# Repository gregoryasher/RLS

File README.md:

# Remote Lab System: Base Station
The Remote Lab System is a system designed for the University of Washington Bothell campus's Electrical Engineering department. This was a Capstone (or Senior) project that concluded our degrees at the University of Washington. We are a group of Computer Engineering students who were enrolled in the program from 2015 to 2017 when we graduated summer quarter. The development of this project was broken up into Spring and Summer quarter 2017.

# Starting Notes
When we chose this as our project we were initially informed the system did not function. At all. What we found towards the end of our first quarter was the system did not work because previous teams did not create or test any of the components or any code to do so. It became apparent we needed to completely redesign the system and create all the code.

We created a project and work schedule and dove in. These schedules were essential to the success of our project.

# Goals
This was the fourth iteration of the Base Station and our design goals were to: 
Add an additional Intronix LogicPort logic analyzer to support a maximum total of 68-channels
Add an 16-bit Analog-to-Digital Converter (ADC)
Improve heat dissipation from linear regulators
Design a stable chassis
Update Graphical User Interface (GUI)
Improve software robustness

# Purpose
The Remote Lab System is designed to allow students to work on lab experiments remotely away from campus, or the lab facilities. This system is a learning tool and study aid allowing students to have unlimited access, at any time of day, to their required lab equipment. Dr. Arnold Berger at the University of Washington Bothell conducted research showing that when students were given the ability to work remotely, the peak times were between midnight and 4:00 am. His research also concluded that female students spent more time connected to the system than male students, and also generally received higher grades on related course content.

While no version of the Remote Lab System has been officially implemented in coursework, we believe our project will increase students understanding of hardware integration by allowing them to quickly change various settings on daughterboard experiments and observe their changes in real time.

# Conclusion
At the end of our Capstone program in Summer quarter 2017 we had successfully achieved our goals. 

We added an additional logic analyzer: allowing the use of the two operating independently (two 34-channel logic analyzers) or dual support (one 68-channel logic analyzer) based on the configuration of the attached daughterboard.

We added a 16-bit ADC, effectively increasing the accuracy of node voltage measurements made by the system by 256 times.

We successfully solved the heat dissipation issue on the linear regulators by increasing the heatsink size and adding a thermally controlled fan circuit. 

We purchased and built a galvanized steel chassis for the system to be housed, complete with rubber feet to reduce vibrations caused by the fan. The motherboard's daughterboard connectors protrude from the lid such that no daughterboard will have clearance issues on the lid. The motherboard is mounted to the lid using brass standoffs threaded to the lid. The Velleman Oscilloscope/Function Generator system is securely mounted to the bottom of the chassis. Connector cables were made long enough such that the lid may be removed from the chassis and placed flat beside it. The fan is securely mounted to the chassis with no interference on the motherboard and in direct line with all four linear regulator heatsinks.

We successfully updated the GUI to improve security and user lockouts. The user can no longer send updated board information to a daughterboard not installed. The user can no longer change settings on a daughterboard not installed. The user is forced to check which board is installed before making any settings changes. 

The GUI now automatically detects the correct communications port for the Remote Lab System. If the Remote Lab System is not detected upon program start-up, a prompt appears warning the user.

Pressing the "Update Board" button now actually updates the board with the user's desired daughterboard settings.

Pressing the "Check Board" button now actually sends a request to read the daughterboard's boardID pin states. It also receives the correct values that were read.

Linear regulators now have supporting code and the values change based on the constructor's inputs. It should be noted that these devices in previous iterations never operated due to a lack of supporting code.

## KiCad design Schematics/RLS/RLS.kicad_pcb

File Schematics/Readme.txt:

This folder contains the schematics for the Motherboard of the Remote Lab System.

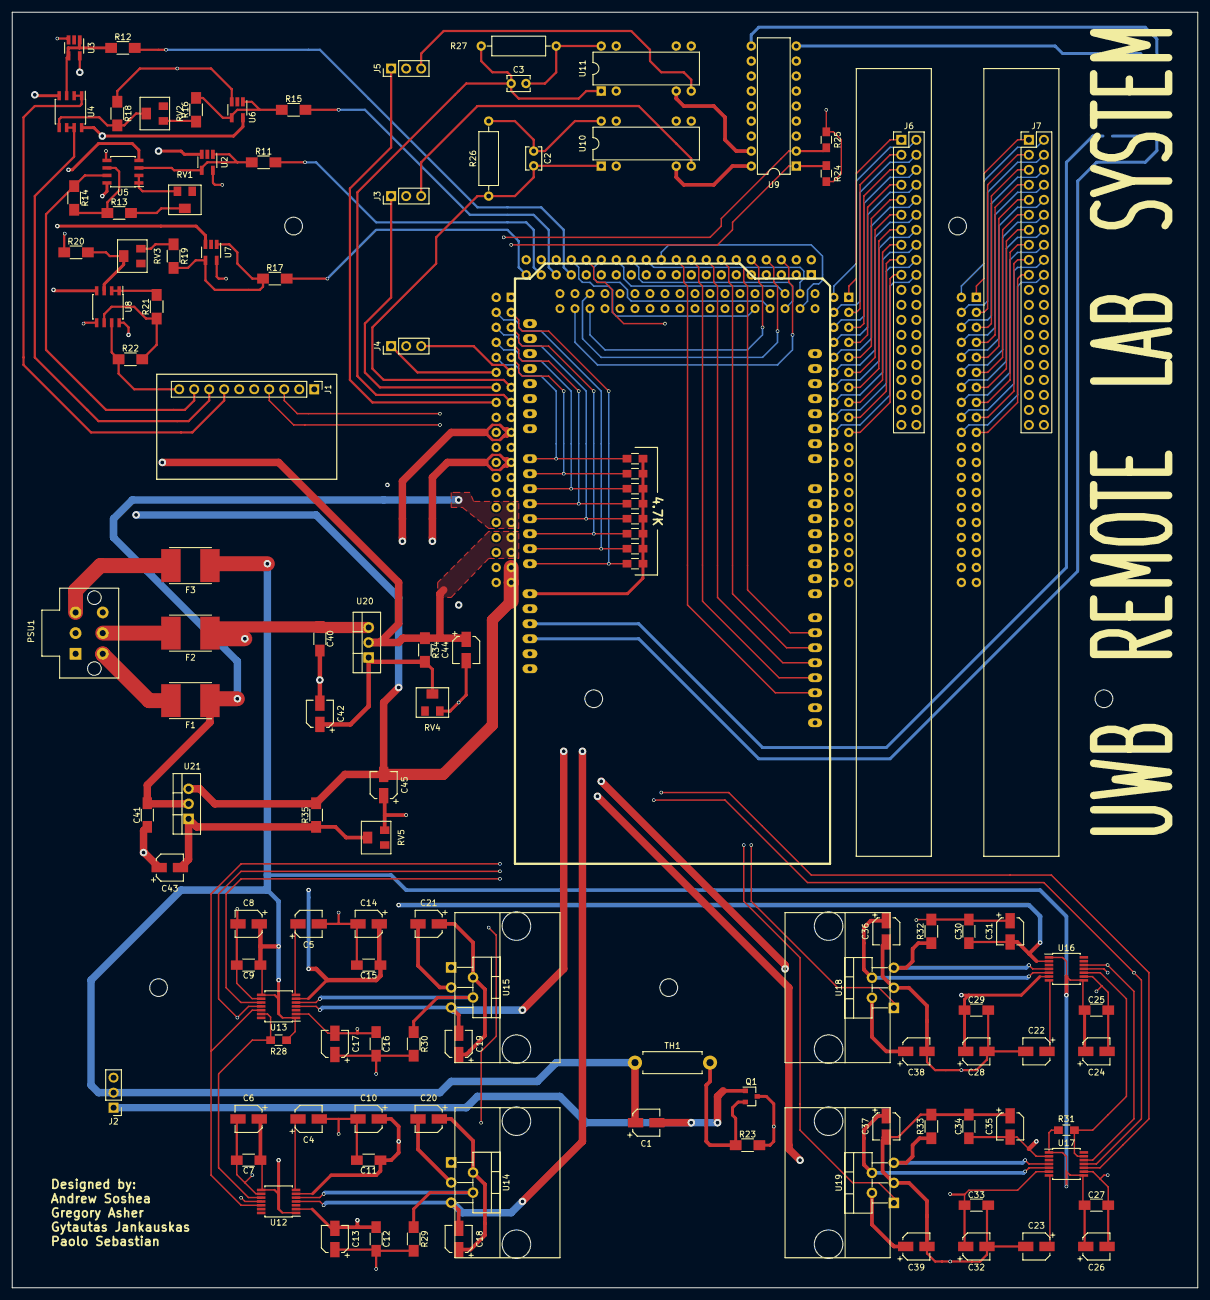
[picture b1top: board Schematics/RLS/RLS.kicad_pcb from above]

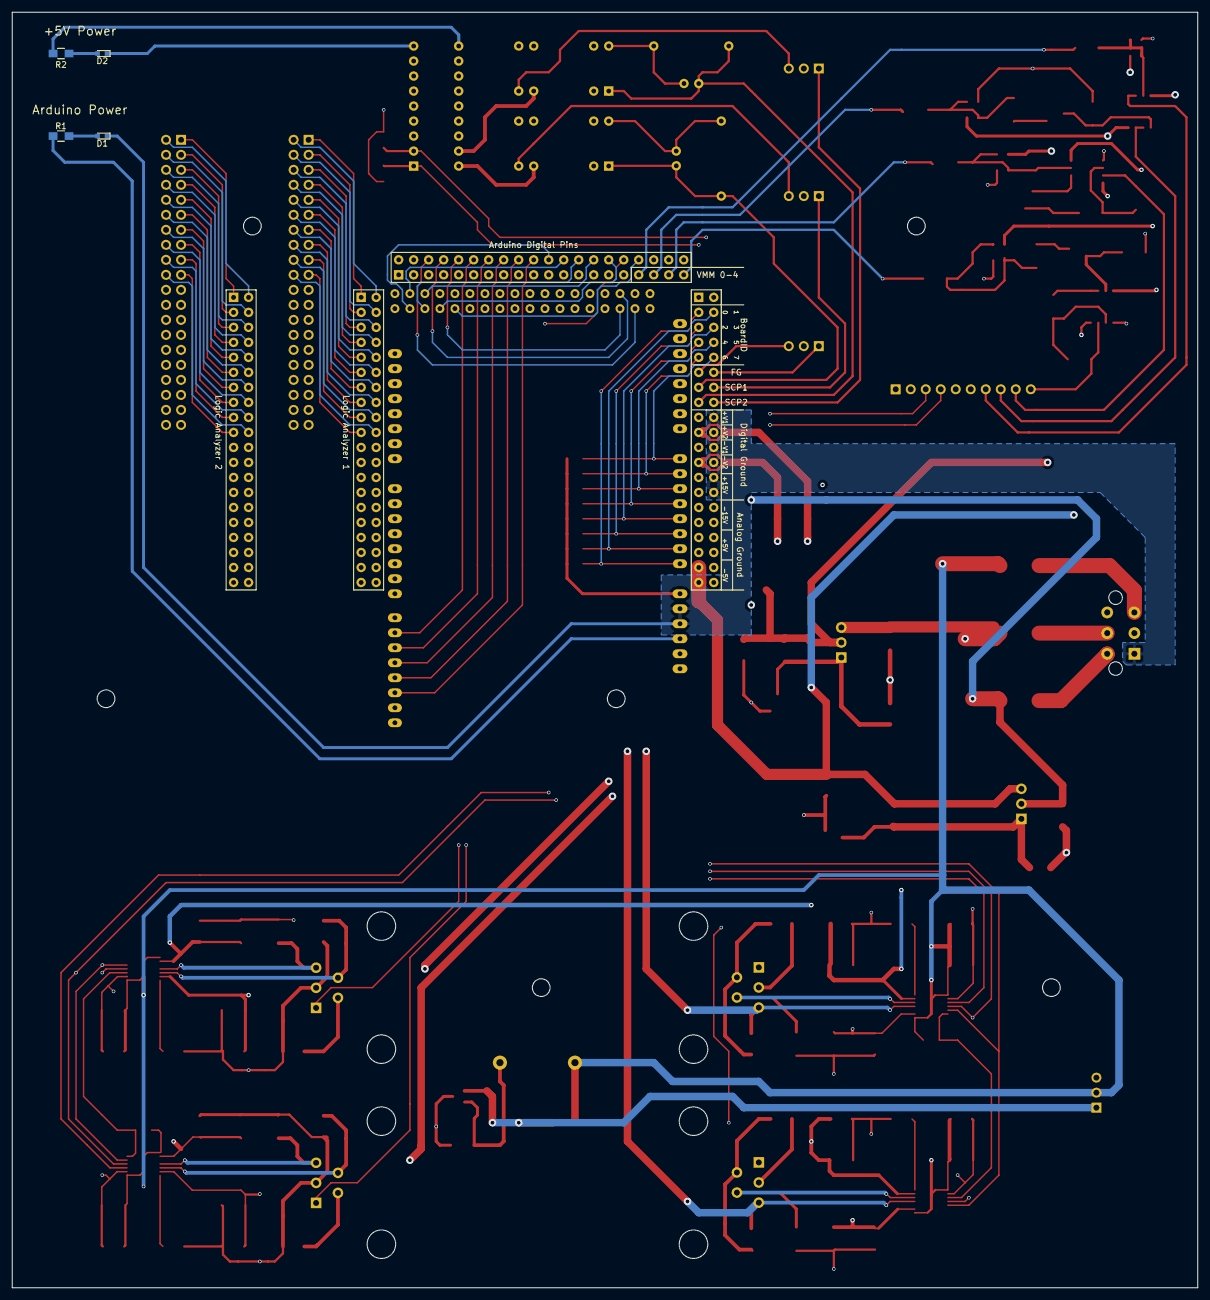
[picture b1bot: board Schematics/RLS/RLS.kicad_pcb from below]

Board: 4 copper layers, 200.7 x 215.9 mm, 122 parts (4 on the bottom side), 188 nets.

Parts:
C1, C6, C8, C10, C13, C14, C17, C18, C19, C20, C21, C24, C26, C28, C31, C32, C35, C36, C37, C38, C39, C42, C43: 10uF; CP_Elec_4x5.3
C2, C3: 15pF; C_Disc_D3.8mm_W2.6mm_P2.50mm
C4, C5, C22, C23, C44, C45: 1uF; CP_Elec_4x5.3
C7, C9, C11, C12, C15, C16, C25, C27, C29, C30, C33, C34, C40, C41: 0.1uF; C_1206_HandSoldering
D1: AD_LED; LED_0603
D2: +5V_LED; LED_0603
DB1: DaughterBoard_Connectors; Daughterboard_4_Conn
F1: 1A; Fuse_SMD_Custom
F2: 1.5A; Fuse_SMD_Custom
F3: 4A; Fuse_SMD_Custom
J1: ADS1115; Pin_Header_Straight_1x10_Pitch2.54mm
J2: DC_Fan; Pin_Header_Straight_1x03_Pitch2.54mm
J3: Velleman_Probe1; Pin_Header_Straight_1x03_Pitch2.54mm
J4: Velleman_FuncGen; Pin_Header_Straight_1x03_Pitch2.54mm
J5: Velleman_Probe2; Pin_Header_Straight_1x03_Pitch2.54mm
J6: Logic_Analyzer1; Pin_Header_Straight_2x20_Pitch2.54mm
J7: Logic_Analyzer2; Pin_Header_Straight_2x20_Pitch2.54mm
PSU1: DIN_5; Molex_2x3_3.5mm
Q1: BS170; SOT-23
R1, R2, R3, R4, R5, R6, R7, R8, R9, R10, R24, R25, R28, R31: 4.7K; R_0805_HandSoldering
R11, R12, R34, R35: 120; R_1206_HandSoldering
R13: 768; R_1206_HandSoldering
R14, R21, R22, R23: 1K; R_1206_HandSoldering
R15, R17, R18, R20: 10K; R_1206_HandSoldering
R16, R19: 9.76K; R_1206_HandSoldering
R26, R27: 9M; R_Axial_DIN0309_L9.0mm_D3.2mm_P12.70mm_Horizontal
R29, R30, R32, R33: 1.78K; R_1206_HandSoldering
RV1, RV2, RV3: 500; Potentiometer_Trimmer_Bourns_PVG5A
RV4, RV5: 1K; Potentiometer_Trimmer_Bourns_PVG5A
TH1: 3K_NTC; R_Axial_DIN0411_L9.9mm_D3.6mm_P12.70mm_Horizontal
U1: ARDUINO_MEGA_SHIELD
U2, U3, U6, U7: RB496EATR; SOT-23-5_HandSoldering
U4, U5, U8: NE5532; SOIC-8_3.9x4.9mm_Pitch1.27mm
U9: ULN2803A; DIP-18_W7.62mm
U10, U11: RA30421051; DIP-8(14)_W7.62mm
U12, U13, U16, U17: AD5293; TSSOP-14_4.4x5mm_Pitch0.65mm
U14, U15: LT3015; TO-220-5_Vertical_Type1_w_Heatsink
U18, U19: LT1963; TO-220-5_Vertical_Type1_w_Heatsink
U20: LM317T; TO-220_Vertical
U21: LM337T; TO-220_Vertical

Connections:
+5V: C1.1, C6.1, C7.1, C8.1, C9.1, C24.1, C25.1, C26.1, C27.1, F3.1, J1.1, J2.2, R2.1, R3.2, R4.2, R5.2, R6.2, R7.2, R8.2, R9.2, R10.2, R24.1, R25.1, R28.2, R31.2, TH1.1, U1.V_IN, U9.10, U10.2, U11.2, U12.1, U12.8, U13.1, U13.8, U16.1, U16.8, U17.1, U17.8
+5V_R: C44.1, DB1.33, DB1.35, R34.1, U3.5, U20.2
+15V: C10.1, C11.1, C14.1, C15.1, C28.1, C29.1, C32.1, C33.1, C38.1, C39.1, C40.1, DB1.25, DB1.27, F2.1, U4.8, U5.8, U6.5, U8.8, U12.6, U13.6, U16.6, U17.6, U18.2, U19.2, U20.3
+V1: C36.1, DB1.17, U16.5, U18.4
+V1_SHDN: U1.AD9, U18.1
+V2: C37.1, DB1.19, U17.5, U19.4
+V2_SHDN: U1.AD8, U19.1
-5V_R: C45.2, DB1.37, DB1.39, R35.2, U2.3, U21.3
-15V: C12.1, C13.2, C16.1, C17.2, C20.2, C21.2, C30.1, C31.2, C34.1, C35.2, C41.2, DB1.29, DB1.31, F1.1, U4.4, U5.4, U7.3, U8.4, U12.2, U13.2, U14.3, U15.3, U16.2, U17.2, U21.2
-V1: C18.2, DB1.21, U12.4, U14.5
-V1_SHDN: U1.AD11, U14.1
-V2: C19.2, DB1.23, U13.4, U15.5
-V2_SHDN: U1.AD10, U15.1
/+5V_-5V_Regulators/+ADJ: C42.1, R34.2, RV4.2, U20.1
/+5V_-5V_Regulators/-ADJ: C43.2, R35.1, RV5.2, U21.1
/ADC_Divder_&_DC_Fan/+5_OVP: R12.1, U3.1, U3.4, U4.3
/ADC_Divder_&_DC_Fan/+15_ADJ: R16.1, RV2.1
/ADC_Divder_&_DC_Fan/+15_DIV: R18.2, RV2.2, U4.5
/ADC_Divder_&_DC_Fan/+15_OVP: R15.1, R16.2, U6.1, U6.4
/ADC_Divder_&_DC_Fan/-5_ADJ: R13.2, RV1.2
/ADC_Divder_&_DC_Fan/-5_BUFF: RV1.3, U5.1, U5.2
/ADC_Divder_&_DC_Fan/-5_INV: R13.1, R14.2, U5.6
/ADC_Divder_&_DC_Fan/-5_OVP: R11.1, U2.1, U2.4, U5.3
/ADC_Divder_&_DC_Fan/-15_ADJ: R19.1, RV3.3
/ADC_Divder_&_DC_Fan/-15_BUFF: R21.2, U8.1, U8.2
/ADC_Divder_&_DC_Fan/-15_DIV: R20.2, RV3.2, U8.3
/ADC_Divder_&_DC_Fan/-15_INV: R21.1, R22.2, U8.6
/ADC_Divder_&_DC_Fan/-15_OVP: R17.1, R19.2, U7.1, U7.4
/ADC_Divder_&_DC_Fan/FAN_GND: C1.2, J2.1, Q1.1
/ADC_Divder_&_DC_Fan/VGS_FAN: Q1.2, R23.1, TH1.2
/ARD_LED: D1.2, R1.2
/BID0: DB1.3, R3.1, U1.AD0
/BID1: DB1.4, R7.1, U1.AD1
/BID2: DB1.5, R4.1, U1.AD2
/BID3: DB1.6, R8.1, U1.AD3
/BID4: DB1.7, R5.1, U1.AD4
/BID5: DB1.8, R9.1, U1.AD5
/BID6: DB1.9, R6.1, U1.AD6
/BID7: DB1.10, R10.1, U1.AD7
/DIN5: F3.2, PSU1.3
/DIN+15: F2.2, PSU1.5
/DIN-15: F1.2, PSU1.4
/Negative_Regulators/-SDO_SDI: R28.1, U12.10, U13.13
/Negative_Regulators/-V1_ADJ: R29.1, U12.5, U14.4
/Negative_Regulators/-V1_EX_C: C4.1, U12.7
/Negative_Regulators/-V2_ADJ: R30.1, U13.5, U15.4
/Negative_Regulators/-V2_EX_C: C5.1, U13.7
/PSU_LED: D2.2, R2.2
/Positive_Regulators/+SDO_SDI: R31.1, U16.10, U17.13
/Positive_Regulators/+V1_ADJ: R32.1, U16.4, U18.5
/Positive_Regulators/+V1_EX_C: C22.1, U16.7
/Positive_Regulators/+V2_ADJ: R33.1, U17.4, U19.5
/Positive_Regulators/+V2_EX_C: C23.1, U17.7
/Scope_Probe_Gain/+SCP1: J3.3, U10.4
/Scope_Probe_Gain/+SCP2: J5.3, U11.4
/Scope_Probe_Gain/SCP1_10X: C2.1, R26.2, U10.8
/Scope_Probe_Gain/SCP2_10X: C3.2, R27.1, U11.8
AA12: R24.2, U1.AD12, U9.1
AA13: R25.2, U1.AD13, U9.2
AA14: DB1.2, U1.AD14
AA15: DB1.1, U1.AD15
AD9: DB1.52, U1.9
AD10: DB1.54, U1.10
AD11: DB1.56, U1.11
AD12: DB1.58, U1.12
AD13: DB1.60, U1.13
AD22: DB1.62, U1.22
AD23: DB1.64, U1.23
AD24: DB1.66, U1.24
AD25: DB1.68, U1.25
AD26: DB1.70, U1.26
AD27: DB1.72, U1.27
AD28: DB1.74, U1.28
AD29: DB1.76, U1.29
AD30: DB1.78, U1.30
AD31: DB1.80, U1.31
AD32: DB1.41, U1.32
AD33: DB1.43, U1.33
AD34: DB1.45, U1.34
AD35: DB1.47, U1.35
AD36: DB1.49, U1.36
AD37: DB1.51, U1.37
AD38: DB1.53, U1.38
AD39: DB1.55, U1.39
AD40: DB1.57, U1.40
AD41: DB1.59, U1.41
AD42: DB1.61, U1.42
AD43: DB1.63, U1.43
AD44: DB1.65, U1.44
AD45: DB1.67, U1.45
AD46: DB1.69, U1.46
AD47: DB1.71, U1.47
AD_LED: R1.1, U1.5V
AGND: C4.2, C5.2, C6.2, C7.2, C8.2, C9.2, C10.2, C11.2, C12.2, C13.1, C14.2, C15.2, C16.2, C17.1, C18.1, C19.1, C20.1, C21.1, C22.2, C23.2, C24.2, C25.2, C26.2, C27.2, C28.2, C29.2, C30.2, C31.1, C32.2, C33.2, C34.2, C35.1, C36.2, C37.2, C38.2, C39.2, C40.2, C41.1, C42.2, C43.1, C44.2, C45.1, D2.1, DB1.30, DB1.32, DB1.34, DB1.36, DB1.38, DB1.40, J1.2, J1.5, PSU1.2, Q1.3, R18.1, R20.1, R23.2, R29.2, R30.2, R32.2, R33.2, RV4.3, RV5.3, U2.5, U3.3, U5.5, U6.3, U7.5, U8.5, U9.9, U12.9, U13.9, U14.2, U15.2, U16.9, U17.9, U18.3, U19.3
AIN0: J1.7, U4.1, U4.2
AIN1: J1.8, U4.6, U4.7
AIN2: J1.9, R14.1, U5.7
AIN3: J1.10, R22.1, U8.7
DGND: D1.1, DB1.18, DB1.20, DB1.22, DB1.24, DB1.26, DB1.28, PSU1.1, U1.GND1, U1.GND2
L1CLK1: DB1.100, J6.20
L1CLK2: DB1.120, J6.40
L1D0: DB1.81, J6.1
L1D1: DB1.82, J6.2
L1D2: DB1.83, J6.3
L1D3: DB1.84, J6.4
L1D4: DB1.85, J6.5
L1D5: DB1.86, J6.6
L1D6: DB1.87, J6.7
L1D7: DB1.88, J6.8
L1D8: DB1.91, J6.11
L1D9: DB1.92, J6.12
L1D10: DB1.93, J6.13
L1D11: DB1.94, J6.14
L1D12: DB1.95, J6.15
L1D13: DB1.96, J6.16
L1D14: DB1.97, J6.17
L1D15: DB1.98, J6.18
L1D16: DB1.101, J6.21
L1D17: DB1.102, J6.22
L1D18: DB1.103, J6.23
L1D19: DB1.104, J6.24
L1D20: DB1.105, J6.25
L1D21: DB1.106, J6.26
L1D22: DB1.107, J6.27
L1D23: DB1.108, J6.28
L1D24: DB1.111, J6.31
L1D25: DB1.112, J6.32
L1D26: DB1.113, J6.33
L1D27: DB1.114, J6.34
L1D28: DB1.115, J6.35
L1D29: DB1.116, J6.36
L1D30: DB1.117, J6.37
L1D31: DB1.118, J6.38
L1GND: DB1.89, DB1.90, DB1.99, DB1.109, DB1.110, DB1.119, J6.9, J6.10, J6.19, J6.29, J6.30, J6.39
L2CLK1: DB1.140, J7.20
L2CLK2: DB1.160, J7.40
L2D0: DB1.121, J7.1
L2D1: DB1.122, J7.2
L2D2: DB1.123, J7.3
L2D3: DB1.124, J7.4
L2D4: DB1.125, J7.5
L2D5: DB1.126, J7.6
L2D6: DB1.127, J7.7
L2D7: DB1.128, J7.8
L2D8: DB1.131, J7.11
L2D9: DB1.132, J7.12
L2D10: DB1.133, J7.13
L2D11: DB1.134, J7.14
L2D12: DB1.135, J7.15
L2D13: DB1.136, J7.16
L2D14: DB1.137, J7.17
L2D15: DB1.138, J7.18
L2D16: DB1.141, J7.21
L2D17: DB1.142, J7.22
L2D18: DB1.143, J7.23
L2D19: DB1.144, J7.24
L2D20: DB1.145, J7.25
L2D21: DB1.146, J7.26
L2D22: DB1.147, J7.27
L2D23: DB1.148, J7.28
L2D24: DB1.151, J7.31
L2D25: DB1.152, J7.32
L2D26: DB1.153, J7.33
L2D27: DB1.154, J7.34
L2D28: DB1.155, J7.35
L2D29: DB1.156, J7.36
L2D30: DB1.157, J7.37
L2D31: DB1.158, J7.38
L2GND: DB1.129, DB1.130, DB1.139, DB1.149, DB1.150, DB1.159, J7.9, J7.10, J7.19, J7.29, J7.30, J7.39
MISO: DB1.50, U1.50
MOSI: DB1.48, U1.51, U13.10, U17.10
NEG_GEN: DB1.12, J4.1
NEG_SCP1: DB1.14, J3.1
NEG_SCP2: DB1.16, J5.1
N_POT_CE: U1.53, U12.12, U13.12
POS_GEN: DB1.11, J4.3
POS_SCP1: C2.2, DB1.13, R26.1, U10.1
POS_SCP2: C3.1, DB1.15, R27.2, U11.1
P_POT_CE: U1.48, U16.12, U17.12
RLY1: U9.18, U10.3
RLY2: U9.17, U11.3
SCL: DB1.42, J1.3, U1.21
SCLK: DB1.46, U1.52, U12.11, U13.11, U16.11, U17.11
SDA: DB1.44, J1.4, U1.20
VM00: DB1.73, R12.2
VM01: DB1.75, R15.2
VM02: DB1.77, R11.2
VM03: DB1.79, R17.2

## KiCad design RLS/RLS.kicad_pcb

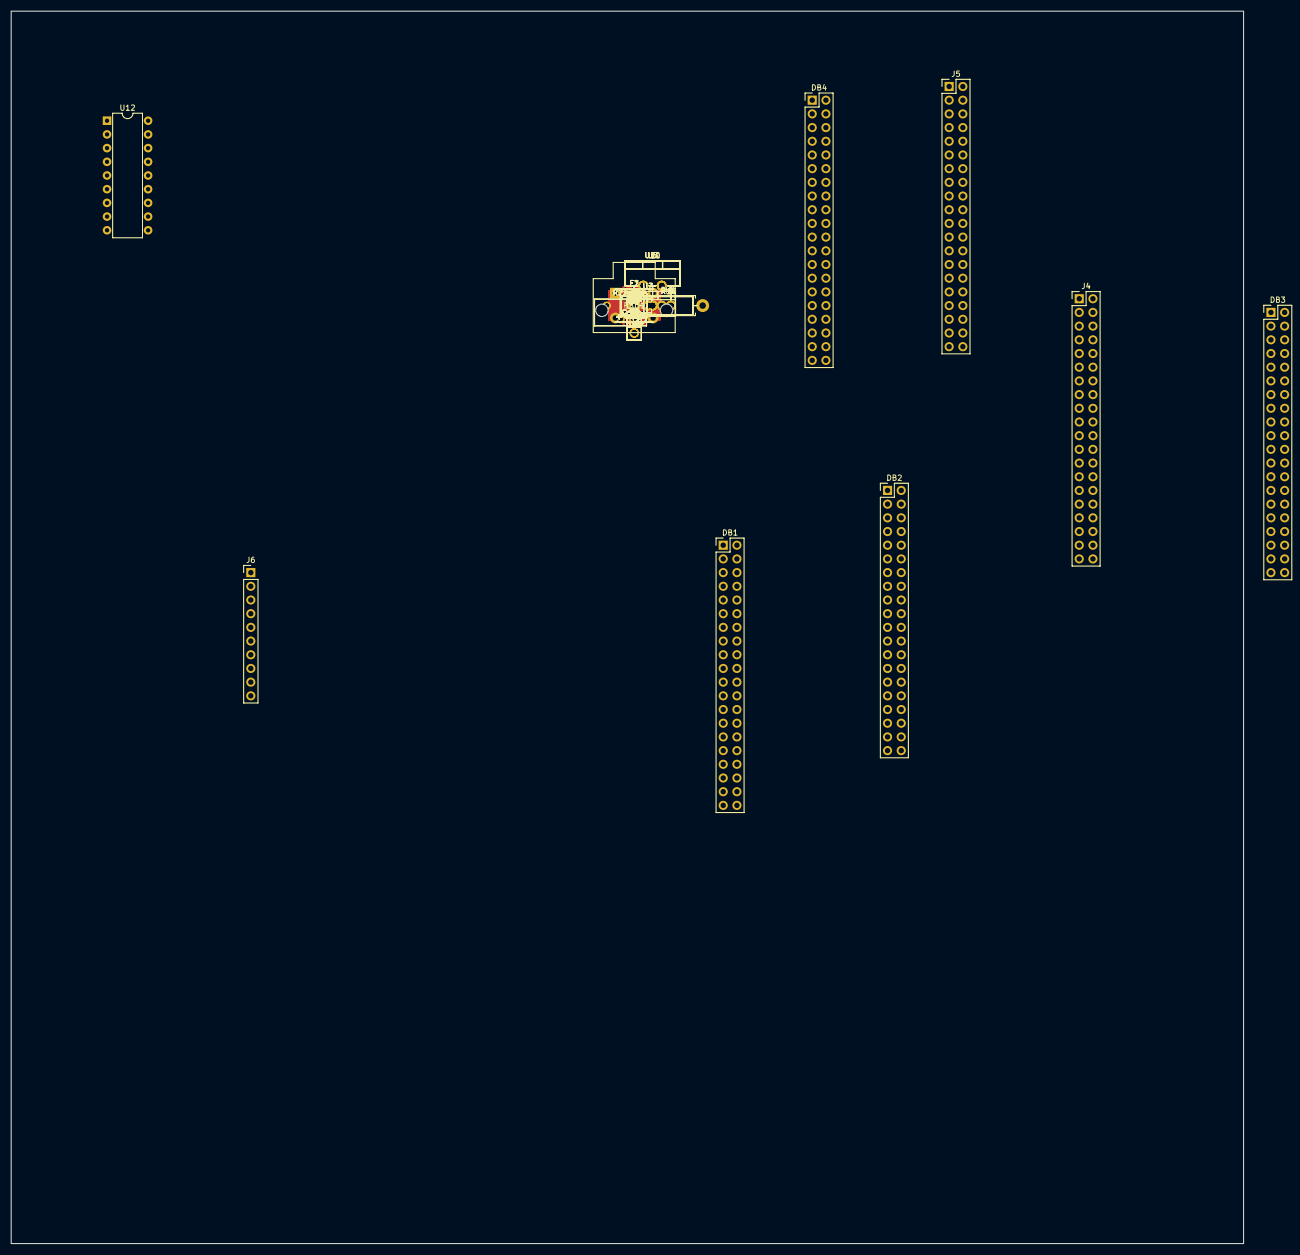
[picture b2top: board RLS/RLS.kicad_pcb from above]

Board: 4 copper layers, 228.6 x 228.6 mm, 108 parts (0 on the bottom side), 131 nets, no tracks yet.

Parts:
C1, C2: 15pF; C_Disc_D3.8mm_W2.6mm_P2.50mm
C3, C5, C7, C9, C11, C13, C17, C18, C19, C20, C21, C23, C25, C27, C29, C31, C35, C36, C37, C38, C41, C42, C45: 10uF; CP_Elec_4x5.3
C4, C6, C8, C10, C12, C14, C22, C24, C26, C28, C30, C32, C39, C40: 0.1uF; C_0603_HandSoldering
C15, C16, C33, C34, C43, C44: 1uF; CP_Elec_4x5.3
D1: AD_LED; LED_0603
D2: +5V_LED; LED_0603
DB1: BoardID_VIN_Scope_FuncGen_DB_CONN; Pin_Header_Straight_2x20_Pitch2.54mm
DB2: Arduino_DB_CONN; Pin_Header_Straight_2x20_Pitch2.54mm
DB3: Logic_Analyzer1_DB_CONN; Pin_Header_Straight_2x20_Pitch2.54mm
DB4: Logic_Analyzer2_DB_CONN; Pin_Header_Straight_2x20_Pitch2.54mm
F1: 1A; Fuse_SMD2920
F2: 1.5A; Fuse_SMD2920
F3: 4A; Fuse_SMD2920
J1: Velleman_Probe1; Pin_Header_Straight_1x03_Pitch2.54mm
J2: Velleman_Probe2; Pin_Header_Straight_1x03_Pitch2.54mm
J3: Velleman_FuncGen; Pin_Header_Straight_1x03_Pitch2.54mm
J4: Logic_Analyzer1; Pin_Header_Straight_2x20_Pitch2.54mm
J5: Logic_Analyzer2; Pin_Header_Straight_2x20_Pitch2.54mm
J6: ADS1115; Pin_Header_Straight_1x10_Pitch2.54mm
J7: DC_Fan; Pin_Header_Straight_1x03_Pitch2.54mm
PSU1: DIN_5; Molex_2x3_3.5mm
Q1: BS170; SOT-23
R1, R2, R3, R4, R5, R6, R7, R8, R9, R10, R19, R22, R30, R31, R32, R33: 4.7K; R_0805_HandSoldering
R11, R13: 20K; R_1206_HandSoldering
R12, R14, R15, R16: 10K; R_1206_HandSoldering
R17, R18: 9M; R_Axial_DIN0309_L9.0mm_D3.2mm_P12.70mm_Horizontal
R20, R21, R23, R24: 1.78K; R_1206_HandSoldering
R25, R28: 120; R_1206_HandSoldering
R26, R27: 1K_POT; Potentiometer_Trimmer_Bourns_3296Y
R29: 1K; R_1206_HandSoldering
TH1: 3K_NTC; R_Axial_DIN0411_L9.9mm_D3.6mm_P12.70mm_Horizontal
U2: LM317T; TO-220_Vertical
U3: LM337T; TO-220_Vertical
U4, U5, U8, U9: AD5293; SSOP-14
U6, U7: LT3015; TO-220-5_Pentawatt_Multiwatt-5_Vertical_StaggeredType1
U10, U11: LT1963; TO-220-5_Pentawatt_Multiwatt-5_Vertical_StaggeredType1
U12: ULN2803A; DIP-18_W7.62mm

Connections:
+5V: C7.1, C8.1, C13.1, C14.1, C25.1, C26.1, C31.1, C32.1, C45.1, F3.1, J6.1, J7.2, R1.1, R2.1, R3.2, R4.2, R5.2, R6.2, R7.2, R8.2, R9.2, R10.2, R19.2, R22.2, R33.1, TH1.1, U4.1, U4.8, U5.1, U5.8, U8.1, U8.8, U9.1, U9.8, U12.10
+5V_R: C43.1, DB1.33, DB1.35, R25.1, U2.2
+15V: C3.1, C4.1, C9.1, C10.1, C21.1, C22.1, C27.1, C28.1, C36.1, C38.1, C39.1, DB1.25, DB1.27, F2.1, U2.3, U4.6, U5.6, U8.6, U9.6, U10.4, U11.2
+V1: C37.1, DB1.17, U9.5, U11.4
+V2: C35.1, DB1.19, U8.5, U10.2
-5V_R: C44.2, DB1.37, DB1.39, R28.2, U3.3
-15V: C5.2, C6.1, C11.2, C12.1, C18.2, C20.2, C23.2, C24.1, C29.2, C30.1, C40.2, DB1.29, DB1.31, F1.1, U3.2, U4.2, U5.2, U6.3, U7.3, U8.2, U9.2
-V1: C19.2, DB1.21, U5.4, U7.5
-V2: C17.2, DB1.23, U4.4, U6.5
AA12: R1.2, U12.1
AA13: R2.2, U12.2
AGND: C3.2, C4.2, C5.1, C6.2, C7.2, C8.2, C9.2, C10.2, C11.1, C12.2, C13.2, C14.2, C15.2, C16.2, C17.1, C18.1, C19.1, C20.1, C21.2, C22.2, C23.1, C24.2, C25.2, C26.2, C27.2, C28.2, C29.1, C30.2, C31.2, C32.2, C33.2, C34.2, C35.2, C36.2, C37.2, C38.2, C39.2, C40.1, C41.2, C42.1, C43.2, C44.1, D1.2, D2.2, DB1.30, DB1.32, DB1.34, DB1.36, DB1.38, DB1.40, J6.2, J6.5, PSU1.2, Q1.3, R12.2, R14.2, R16.2, R20.2, R21.2, R23.2, R24.2, R26.3, R27.1, R29.2, U4.9, U5.9, U6.2, U7.2, U8.9, U9.9, U10.3, U11.3, U12.9
BID0: DB1.3, R6.1
BID1: DB1.4, R7.1
BID2: DB1.5, R5.1
BID3: DB1.6, R8.1
BID4: DB1.7, R4.1
BID5: DB1.8, R9.1
BID6: DB1.9, R3.1
BID7: DB1.10, R10.1
DGND: DB1.18, DB1.20, DB1.22, DB1.24, DB1.26, DB1.28, PSU1.1
L1CLK1: DB3.20, J4.20
L1CLK2: DB3.40, J4.40
L1D0: DB3.1, J4.1
L1D1: DB3.2, J4.2
L1D2: DB3.3, J4.3
L1D3: DB3.4, J4.4
L1D4: DB3.5, J4.5
L1D5: DB3.6, J4.6
L1D6: DB3.7, J4.7
L1D7: DB3.8, J4.8
L1D8: DB3.11, J4.11
L1D9: DB3.12, J4.12
L1D10: DB3.13, J4.13
L1D11: DB3.14, J4.14
L1D12: DB3.15, J4.15
L1D13: DB3.16, J4.16
L1D14: DB3.17, J4.17
L1D15: DB3.18, J4.18
L1D16: DB3.21, J4.21
L1D17: DB3.22, J4.22
L1D18: DB3.23, J4.23
L1D19: DB3.24, J4.24
L1D20: DB3.25, J4.25
L1D21: DB3.26, J4.26
L1D22: DB3.27, J4.27
L1D23: DB3.28, J4.28
L1D24: DB3.31, J4.31
L1D25: DB3.32, J4.32
L1D26: DB3.33, J4.33
L1D27: DB3.34, J4.34
L1D28: DB3.35, J4.35
L1D29: DB3.36, J4.36
L1D30: DB3.37, J4.37
L1D31: DB3.38, J4.38
L1GND: DB3.9, DB3.10, DB3.19, DB3.29, DB3.30, DB3.39, J4.9, J4.10, J4.19, J4.29, J4.30, J4.39
L2CLK1: DB4.20, J5.20
L2CLK2: DB4.40, J5.40
L2D0: DB4.1, J5.1
L2D1: DB4.2, J5.2
L2D2: DB4.3, J5.3
L2D3: DB4.4, J5.4
L2D4: DB4.5, J5.5
L2D5: DB4.6, J5.6
L2D6: DB4.7, J5.7
L2D7: DB4.8, J5.8
L2D8: DB4.11, J5.11
L2D9: DB4.12, J5.12
L2D10: DB4.13, J5.13
L2D11: DB4.14, J5.14
L2D12: DB4.15, J5.15
L2D13: DB4.16, J5.16
L2D14: DB4.17, J5.17
L2D15: DB4.18, J5.18
L2D16: DB4.21, J5.21
L2D17: DB4.22, J5.22
L2D18: DB4.23, J5.23
L2D19: DB4.24, J5.24
L2D20: DB4.25, J5.25
L2D21: DB4.26, J5.26
L2D22: DB4.27, J5.27
L2D23: DB4.28, J5.28
L2D24: DB4.31, J5.31
L2D25: DB4.32, J5.32
L2D26: DB4.33, J5.33
L2D27: DB4.34, J5.34
L2D28: DB4.35, J5.35
L2D29: DB4.36, J5.36
L2D30: DB4.37, J5.37
L2D31: DB4.38, J5.38
L2GND: DB4.9, DB4.10, DB4.19, DB4.29, DB4.30, DB4.39, J5.9, J5.10, J5.19, J5.29, J5.30, J5.39
MOSI: U4.10, U8.10
NEG_GEN: DB1.12, J3.1
NEG_SCP1: DB1.14, J1.1
NEG_SCP2: DB1.16, J2.1
N_POT_CE: U4.12, U5.12
unnamed: C1.1, R17.2
unnamed: C2.1, R18.2
unnamed: C15.1, U5.7
unnamed: C16.1, U4.7
unnamed: C33.1, U9.7
unnamed: C34.1, U8.7
unnamed: C41.1, R25.2, R26.2, U2.1
unnamed: C42.2, R27.2, R28.1, U3.1
unnamed: C45.2, J7.1, Q1.1
unnamed: D1.1, R30.2
unnamed: D2.1, R31.2
unnamed: F1.2, PSU1.4
unnamed: F2.2, PSU1.5
unnamed: F3.2, PSU1.3
unnamed: Q1.2, R29.1, TH1.2
unnamed: R19.1, U4.13, U5.10
unnamed: R20.1, U4.5, U6.4
unnamed: R21.1, U5.5, U7.4
unnamed: R22.1, U8.13, U9.10
unnamed: R23.1, U9.4, U11.5
unnamed: R24.1, U8.4, U10.1
unnamed: R30.1, R32.2
unnamed: R31.1, R33.2
POS_GEN: DB1.11, J3.3
POS_SCP1: C1.2, DB1.13, R17.1
POS_SCP2: C2.2, DB1.15, R18.1
P_POT_CE: U8.12, U9.12
SCLK: U4.11, U5.11, U8.11, U9.11
VD01: J6.8, R15.2, R16.1
VD02: J6.9, R13.2, R14.1
VD03: J6.10, R11.2, R12.1
VM00: DB2.33, J6.7
VM01: DB2.35, R15.1
VM02: DB2.37, R13.1
VM03: DB2.39, R11.1

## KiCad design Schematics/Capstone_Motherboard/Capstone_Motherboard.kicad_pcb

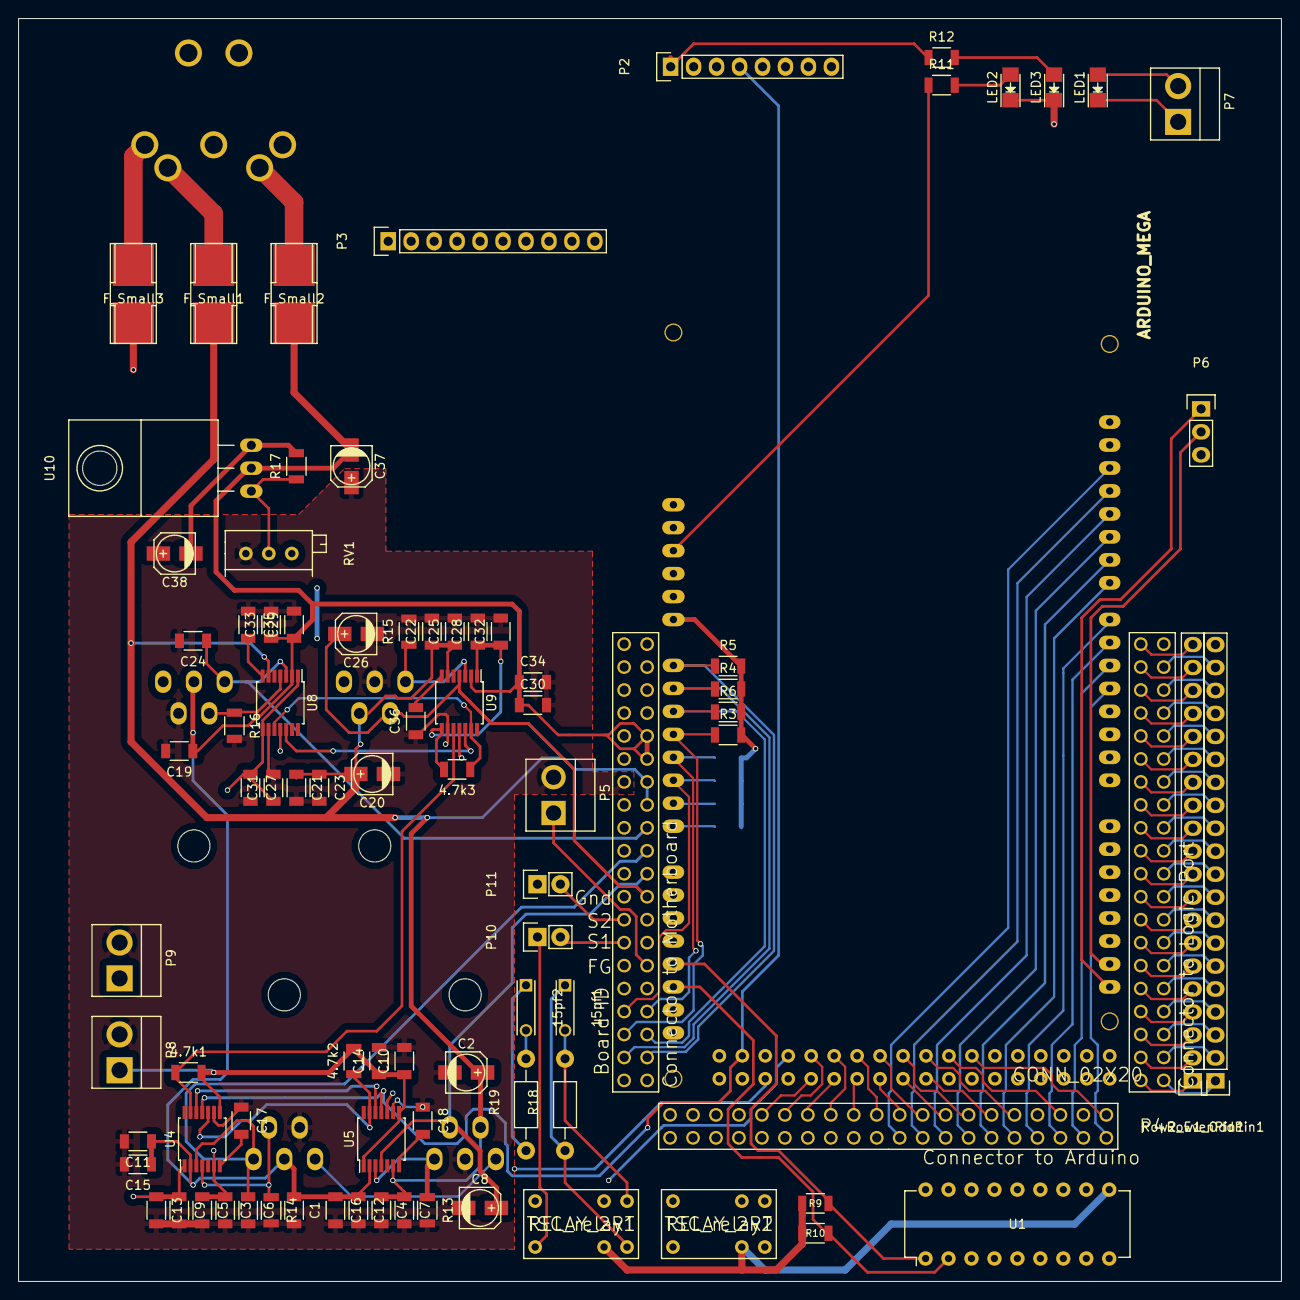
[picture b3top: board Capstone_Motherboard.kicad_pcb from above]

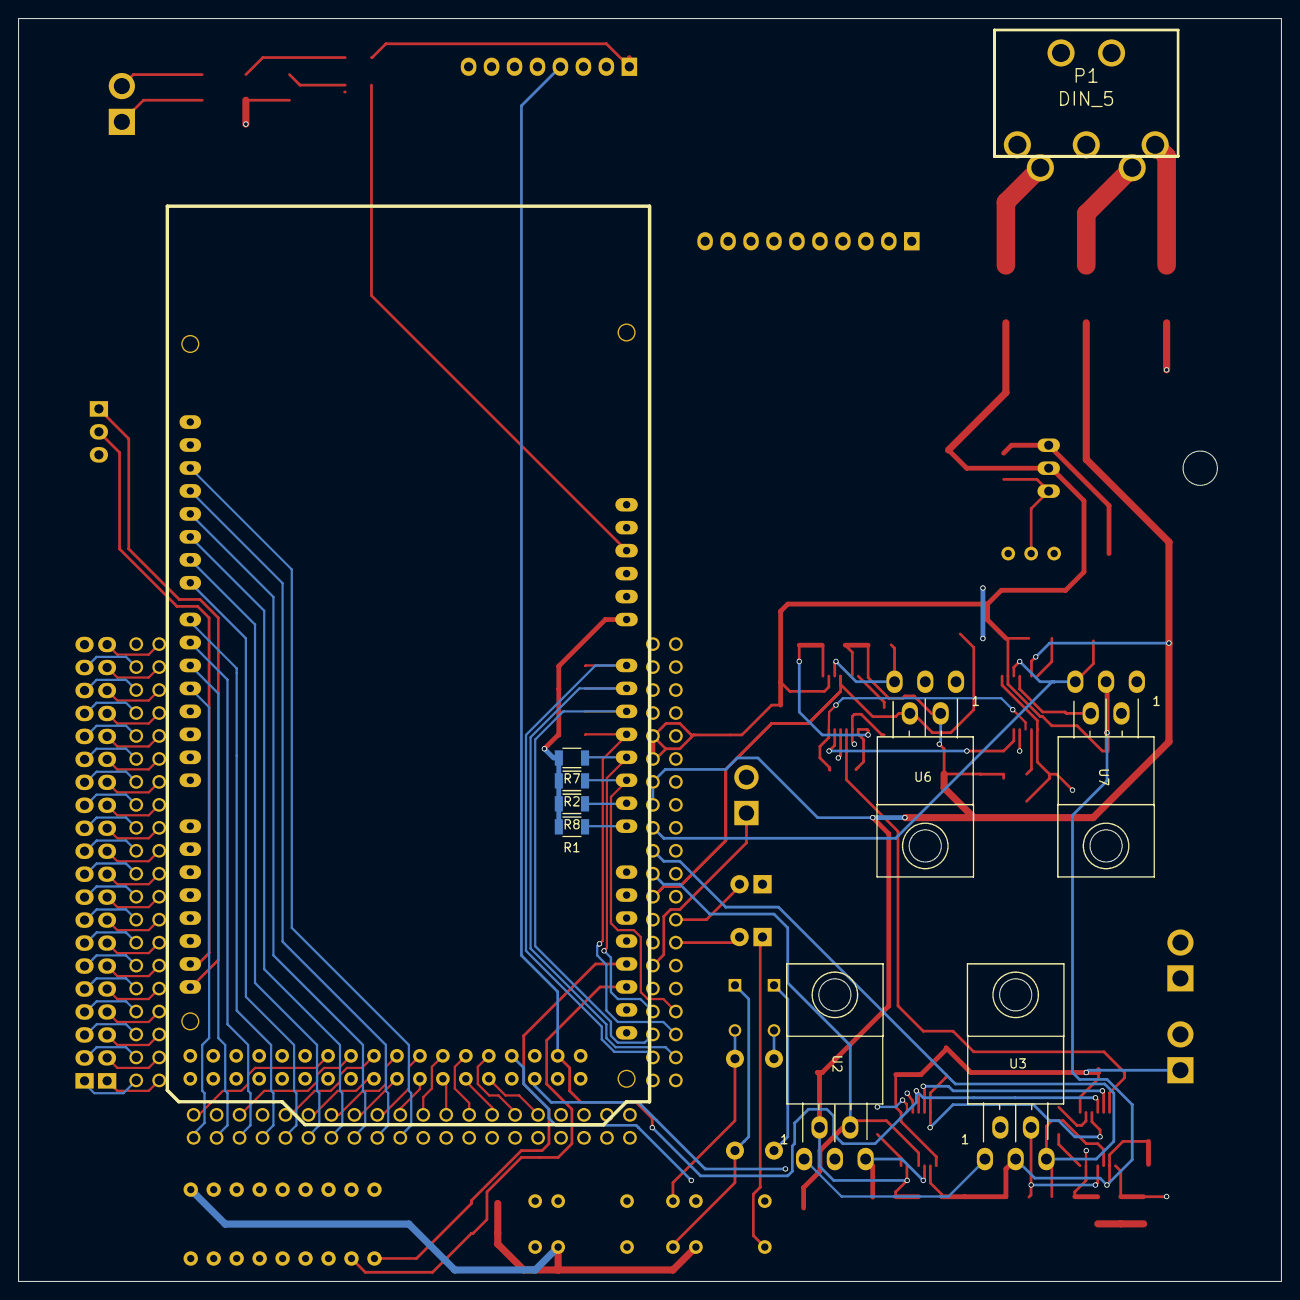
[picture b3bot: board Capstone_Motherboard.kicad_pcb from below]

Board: 4 copper layers, 139.7 x 139.7 mm, 94 parts (9 on the bottom side), 100 nets.

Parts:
4.7k1, 4.7k2, 4.7k3: R; R_1206
15pf1, 15pf2: C_Small; C_Disc_D6_P5
C1, C5, C6, C7, C13, C14, C15, C16, C19, C23, C24, C25, C31, C32, C33, C34: 10uF; C_1206
C2, C8, C20, C26: 10uF; c_elec_4x5.7
C3, C4, C9, C10, C11, C12, C21, C22, C27, C28, C29, C30: 0.1uF; C_1206
C17, C18, C35, C36: 1uF; C_1206
C37: 1uf; c_elec_4x5.8
C38: 10uf; c_elec_4x5.8
F_Small1: 1.5A; Fuse_SMD
F_Small2: 1A; Fuse_SMD
F_Small3: 4A; Fuse_SMD
LED1: Scope; LED-1206
LED2: Ard; LED-1206
LED3: PWR; LED-1206
P1: DIN_5
P2: Micro_SD; Pin_Header_Straight_1x08
P3: CONN_01X10; Pin_Header_Straight_1x10
P4: CONN_02X20; 40pinRevised
P5: FG_input; Pin_Header_Straight_1x02_Pitch3.96mm_Friction_Lock
P6: Clock_Test_Point; Pin_Header_Straight_1x03
P7: FG_LED; Pin_Header_Straight_1x02_Pitch3.96mm_Friction_Lock
P8, P9: Fan_out; Pin_Header_Straight_1x02_Pitch3.96mm_Friction_Lock
P10: Vellemen_prob1; Pin_Header_Straight_1x02
P11: Vellemen_prob2; Pin_Header_Straight_1x02
R1, R2, R3, R4, R5, R6, R7, R8, R9, R10: 4.7k; R_1206
R11, R12: 100; R_1206
R13, R14, R15, R16: 1k; R_1206
R17: R; R_1206
R18, R19: 9M; Resistor_Horizontal_RM10mm
RV1: POT; Potentiometer_Bourns_3296X_3-8Zoll_Inline_ScrewFront
Row1_OddPin1, Row2_EvenPin1: CONN_01X20; Pin_Header_Straight_1x20
TSC_relay1, TSC_relay2: RELAY_2RT; TSC
U1: ULN2803A; DIP-18_W7.62mm
U2, U6: LT1963; Pentawatt_Neutral_Staggered-Typ1_Horizontal_TO220-5-TA05B
U3, U7: LT3015; Pentawatt_Neutral_Staggered-Typ1_Horizontal_TO220-5-TA05B
U4, U5, U8, U9: AD5293; TSSOP-14_4.4x5mm_Pitch0.65mm
U10: LM337T; TO-220_Neutral123_Horizontal

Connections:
5V+: 4.7k1.2, 4.7k2.2, 4.7k3.2, C9.1, C10.1, C13.1, C14.1, C27.1, C28.1, C31.1, C32.1, F_Small3.1, P2.1, P3.1, P4.6, P4.8, P8.1, P9.1, R1.2, R2.2, R3.2, R4.2, R5.2, R6.2, R7.2, R8.2, R9.1, R10.1, R12.1, TSC_relay1.5, TSC_relay2.5, U1.10, U4.1, U4.8, U5.1, U5.8, U8.1, U8.8, U9.1, U9.8
5V-: C38.2, P4.2, P4.4, R17.2, U10.3
15V+: C2.1, C3.1, C4.1, C5.1, C7.1, C20.1, C21.1, C22.1, C23.1, C25.1, F_Small1.1, P4.14, P4.16, U2.2, U4.6, U5.6, U6.2, U8.6, U9.6
15V-: C1.1, C11.1, C12.1, C15.1, C16.1, C19.1, C29.1, C30.1, C33.1, C34.1, C37.2, F_Small2.1, P4.10, P4.12, U3.3, U4.2, U5.2, U7.3, U8.2, U9.2, U10.2
A0: P4.110, Row2_EvenPin1.6
A1: P4.109, Row1_OddPin1.6
A2: P4.108, Row2_EvenPin1.7
A3: P4.107, Row1_OddPin1.7
A4: P4.106, Row2_EvenPin1.8
A5: P4.105, Row1_OddPin1.8
A6: P4.104, Row2_EvenPin1.9
A7: P4.103, Row1_OddPin1.9
A8: P4.100, Row2_EvenPin1.11
A9: P4.99, Row1_OddPin1.11
A10: P4.98, Row2_EvenPin1.12
A11: P4.97, Row1_OddPin1.12
A12: P4.96, Row2_EvenPin1.13
A13: P4.95, Row1_OddPin1.13
A14: P4.94, Row2_EvenPin1.14
A15: P4.93, Row1_OddPin1.14
Ara00: P4.38, R5.1
Ara01: P4.37, R4.1
Ara02: P4.36, R6.1
Ara03: P4.35, R3.1
Ara04: P4.34, R7.1
Ara05: P4.33, R2.1
Ara06: P4.32, R8.1
Ara07: P4.31, R1.1
Ara08: U2.1, U3.1
Ara09: U6.1, U7.1
Ara12: R9.2, U1.1
Ara13: R10.2, U1.2
Ard48: U4.12, U5.12, U8.12, U9.12
Ard51: P2.6, U5.10
Ard52: P2.4, U4.11, U5.11, U8.11, U9.11
CLK: P4.101, Row1_OddPin1.10
D0: P4.120, Row2_EvenPin1.1
D1: P4.119, Row1_OddPin1.1
D2: P4.118, Row2_EvenPin1.2
D3: P4.117, Row1_OddPin1.2
D4: P4.116, Row2_EvenPin1.3
D5: P4.115, Row1_OddPin1.3
D6: P4.114, Row2_EvenPin1.4
D7: P4.113, Row1_OddPin1.4
FG+: P4.30, P5.1
FG-: C1.2, C2.2, C3.2, C4.2, C5.2, C6.2, C7.2, C8.2, C9.2, C10.2, C11.2, C12.2, C13.2, C14.2, C15.2, C16.2, C17.1, C18.1, C19.2, C20.2, C21.2, C22.2, C23.2, C24.2, C25.2, C26.2, C27.2, C28.2, C29.2, C30.2, C31.2, C32.2, C33.2, C34.2, C35.1, C36.1, C37.1, C38.1, LED2.1, LED3.1, P1.5, P2.3, P3.2, P3.5, P4.13, P4.15, P4.17, P4.19, P4.21, P4.23, P4.29, P5.2, P6.3, P8.2, P9.2, R13.2, R14.2, R15.2, R16.2, RV1.1, U1.9, U2.3, U3.2, U4.9, U5.9, U6.3, U7.2, U8.9, U9.9
GNDA: P1.3, P4.1, P4.3, P4.5, P4.7, P4.9, P4.11
Log9: P4.112, Row2_EvenPin1.5
Log10: P4.111, Row1_OddPin1.5
Log19: P4.102, Row2_EvenPin1.10
Log29: P4.92, Row2_EvenPin1.15
Log30: P4.91, Row1_OddPin1.15
Log39: P4.82, Row2_EvenPin1.20
unnamed: 4.7k1.1, U4.13, U9.10
unnamed: 4.7k2.1, U4.10, U5.13
unnamed: 4.7k3.1, U8.10, U9.13
unnamed: 15pf1.1, R18.1, TSC_relay1.6
unnamed: 15pf2.1, R19.1, TSC_relay2.6
unnamed: C17.2, U4.7
unnamed: C18.2, U5.7
unnamed: C35.2, U8.7
unnamed: C36.2, U9.7
unnamed: F_Small1.2, P1.2
unnamed: F_Small2.2, P1.4
unnamed: F_Small3.2, P1.1
unnamed: LED1.1, P7.1
unnamed: LED1.2, P7.2
unnamed: LED2.2, R11.2
unnamed: LED3.2, R12.2
unnamed: P10.1, TSC_relay1.4
unnamed: P11.1, TSC_relay2.4
unnamed: R13.1, U2.5, U5.3
unnamed: R14.1, U3.4, U4.4
unnamed: R15.1, U6.5, U9.3
unnamed: R16.1, U7.4, U8.4
unnamed: R17.1, RV1.2, U10.1
Relay1: TSC_relay1.2, U1.18
Relay2: TSC_relay2.2, U1.17
SCL: P3.3, P6.1
SDA: P3.4, P6.2
Scope1+: 15pf1.2, P4.28, R18.2, TSC_relay1.1
Scope1-: P4.27, P10.2
Scope2+: 15pf2.2, P4.26, R19.2, TSC_relay2.1
Scope2-: P4.25, P11.2
V1+: C8.1, P4.22, U2.4, U5.4
V1-: C6.1, P4.20, U3.5, U4.3
V2+: C26.1, P4.24, U6.4, U9.4
V2-: C24.1, P4.18, U7.5, U8.3
VoMeter_A0: P3.7, P4.48
VoMeter_A1: P3.8, P4.46
VoMeter_A2: P3.9, P4.44
VoMeter_A3: P3.10, P4.42
~CSRAM: P4.87, Row1_OddPin1.17
~CSROM: P4.86, Row2_EvenPin1.18
~M1: P4.85, Row1_OddPin1.18
~MREQ: P4.88, Row2_EvenPin1.17
~RD: P4.89, Row1_OddPin1.16
~RFSH: P4.83, Row1_OddPin1.19
~RST: P4.84, Row2_EvenPin1.19
~WR: P4.90, Row2_EvenPin1.16
